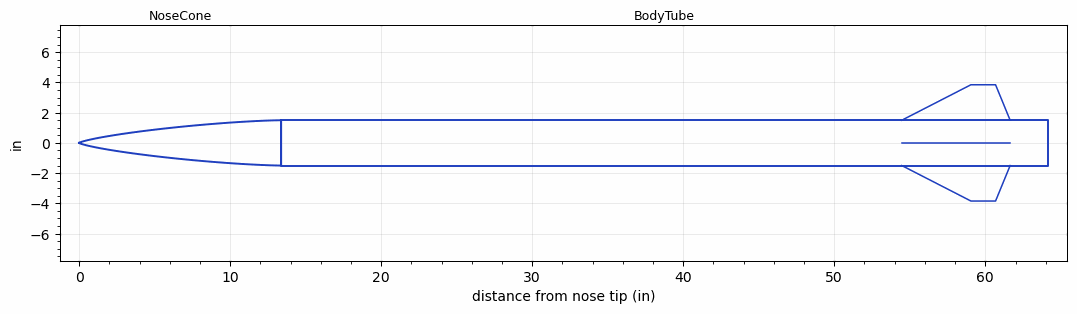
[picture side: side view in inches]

<RASAeroDocument>
 <FileVersion>2</FileVersion>
 <RocketDesign>
  <NoseCone>
   <Length>13.375</Length>
   <Diameter>3</Diameter>
   <Shape>Von Karman Ogive</Shape>
   <Location>0</Location>
  </NoseCone>
  <BodyTube>
   <Length>50.77</Length>
   <Diameter>3</Diameter>
   <Location>13.375</Location>
   <Fin>
    <Count>4</Count>
    <Chord>7.175</Chord>
    <Span>2.35</Span>
    <SweepDistance>4.579</SweepDistance>
    <TipChord>1.63</TipChord>
    <Thickness>0.125</Thickness>
    <LERadius>0.08</LERadius>
    <Location>9.675</Location>
    <AirfoilSection>Hexagonal</AirfoilSection>
    <FX1>0.225</FX1>
    <FX3>0.225</FX3>
   </Fin>
  </BodyTube>
  <Surface>Rough Camouflage Paint</Surface>
  <ModifiedBarrowman>True</ModifiedBarrowman>
  <Turbulence>True</Turbulence>
  <UseBooster1>False</UseBooster1>
  <UseBooster2>False</UseBooster2>
 </RocketDesign>
 <LaunchSite>
  <Altitude>3000</Altitude>
  <Pressure>0</Pressure>
  <RodAngle>2</RodAngle>
  <RodLength>20</RodLength>
  <Temperature>85</Temperature>
  <WindSpeed>8</WindSpeed>
 </LaunchSite>
 <Recovery>
  <Altitude1>1000</Altitude1>
  <Altitude2>1000</Altitude2>
  <DeviceType1>None</DeviceType1>
  <DeviceType2>None</DeviceType2>
  <Event1>False</Event1>
  <Event2>False</Event2>
  <Size1>1</Size1>
  <Size2>1</Size2>
  <EventType1>None</EventType1>
  <EventType2>None</EventType2>
  <CD1>1.33</CD1>
  <CD2>1.33</CD2>
 </Recovery>
 <SimulationList>
  <Simulation>
   <SustainerEngine>L-818  (L-818)</SustainerEngine>
   <SustainerLaunchWt>21.2</SustainerLaunchWt>
   <SustainerNozzleDiameter>2.95</SustainerNozzleDiameter>
   <SustainerCG>41.06</SustainerCG>
   <SustainerIgnitionDelay>0</SustainerIgnitionDelay>
   <Booster1SeparationDelay>0</Booster1SeparationDelay>
   <Booster1IgnitionDelay>0</Booster1IgnitionDelay>
   <IncludeBooster1>False</IncludeBooster1>
   <Booster2Delay>0</Booster2Delay>
   <IncludeBooster2>False</IncludeBooster2>
   <TimetoApogee>31.27062</TimetoApogee>
   <MaxAltitude>15898.28</MaxAltitude>
   <MaxVelocity>1240.228</MaxVelocity>
  </Simulation>
 </SimulationList>
</RASAeroDocument>
